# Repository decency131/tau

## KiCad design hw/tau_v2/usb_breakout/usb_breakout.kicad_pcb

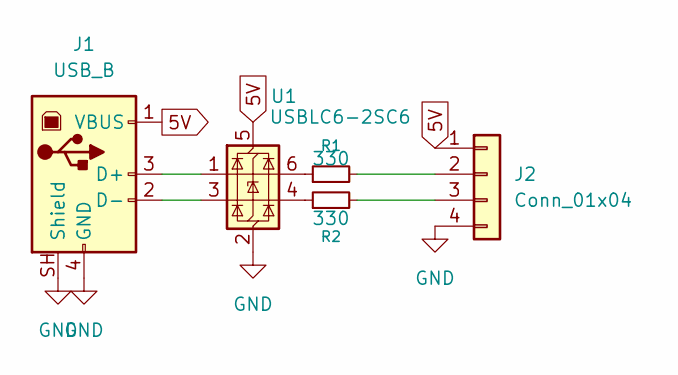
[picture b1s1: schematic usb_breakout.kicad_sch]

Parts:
J1: USB_B; USB_B_OST_USB-B1HSxx_Horizontal
J2: Conn_01x04; PinHeader_1x04_P2.00mm_Vertical
R1, R2: 330; R_0805_2012Metric_Pad1.20x1.40mm_HandSolder
U1: USBLC6-2SC6; SOT-23-6

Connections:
5V: J1.1 (VBUS), J2.1, U1.5 (VBUS)
GND: J1.4 (GND), J1.SH (Shield), J2.4, U1.2 (GND)
unnamed: J1.3 (D+), U1.1 (I/O1)
unnamed: J1.2 (D-), U1.3 (I/O2)
unnamed: J2.2, R1.2
unnamed: J2.3, R2.2
unnamed: R1.1, U1.6 (I/O1)
unnamed: R2.1, U1.4 (I/O2)

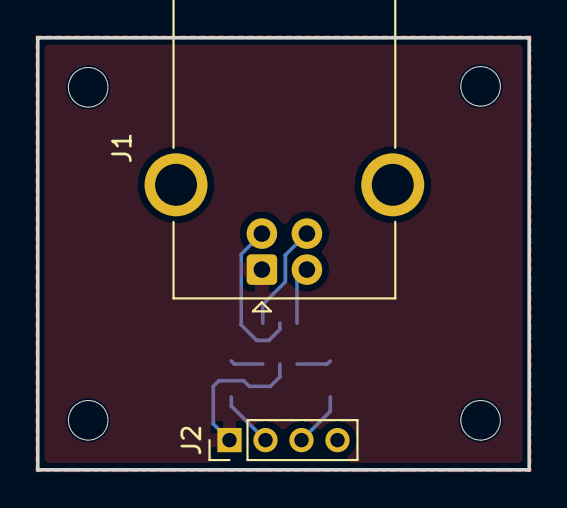
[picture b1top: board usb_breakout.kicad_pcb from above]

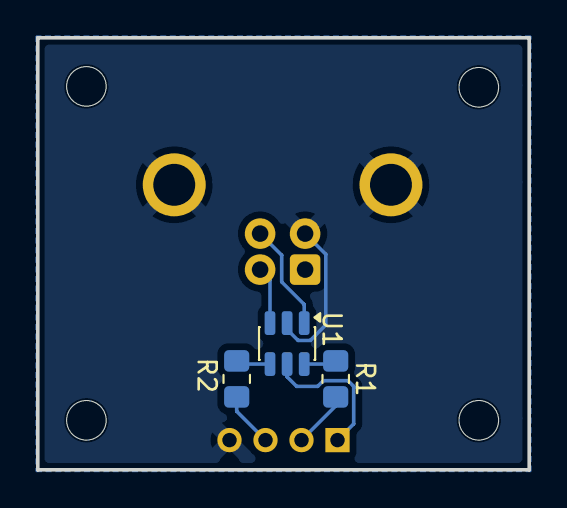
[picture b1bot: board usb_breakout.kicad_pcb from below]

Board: 2 copper layers, 27.3 x 24.0 mm, 9 parts (3 on the bottom side), 8 nets.

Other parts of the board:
M1, M2, M3, M4: MountingHole_2.2mm_M2

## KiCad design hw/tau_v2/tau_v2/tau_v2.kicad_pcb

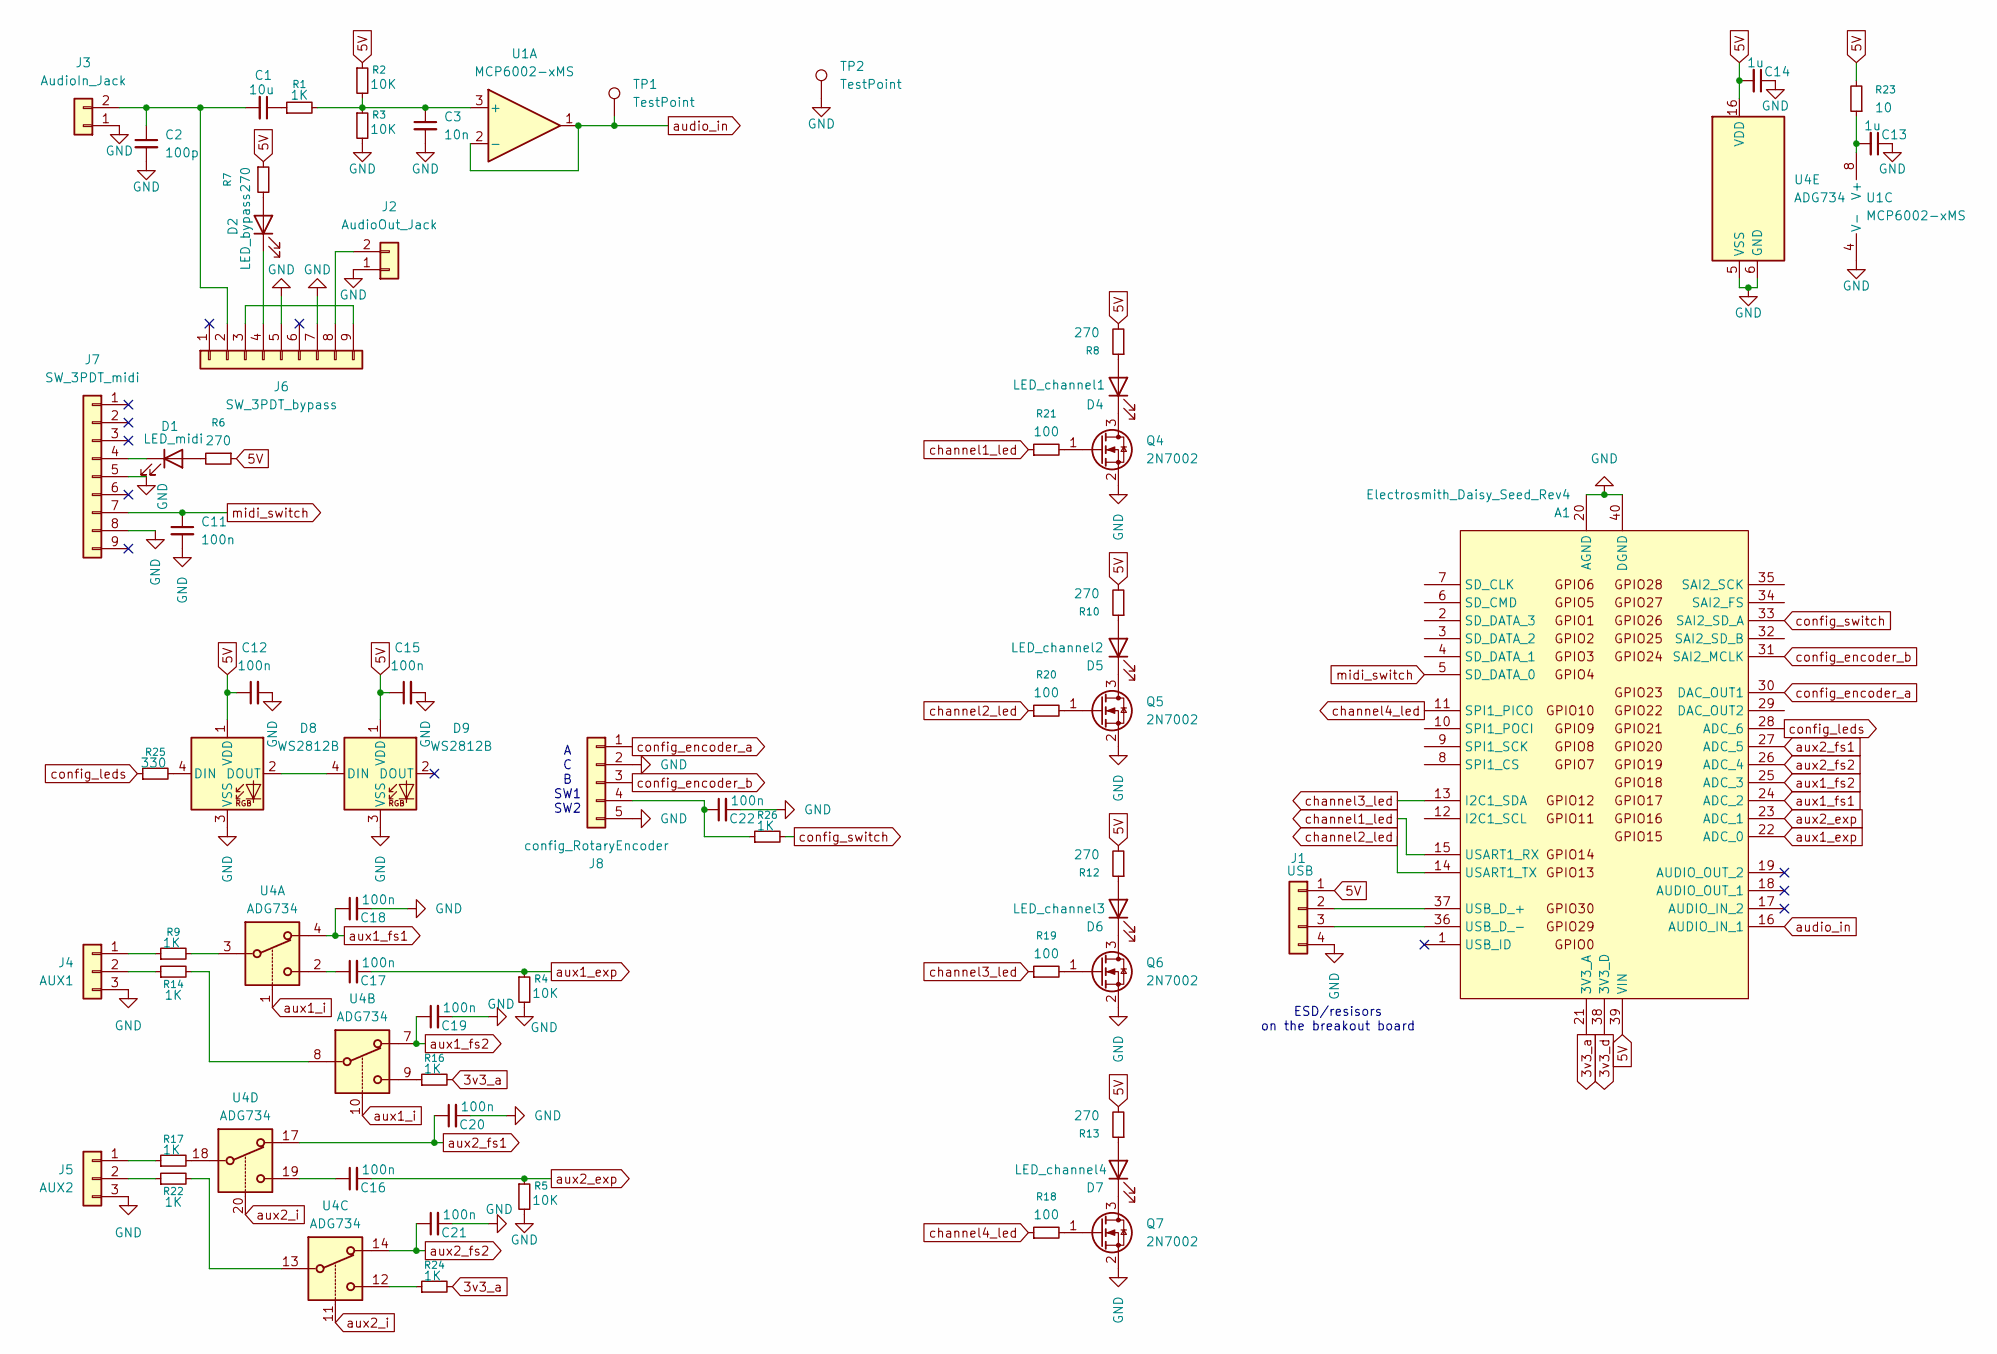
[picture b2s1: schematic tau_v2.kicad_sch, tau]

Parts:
A1: Electrosmith_Daisy_Seed_Rev4; Electrosmith_Daisy_Seed
C1: 10u; C_0805_2012Metric_Pad1.18x1.45mm_HandSolder
C2: 100p; C_0805_2012Metric_Pad1.18x1.45mm_HandSolder
C3: 10n; C_0805_2012Metric_Pad1.18x1.45mm_HandSolder
C11, C12, C15, C16, C17, C18, C19, C20, C21, C22: 100n; C_0805_2012Metric_Pad1.18x1.45mm_HandSolder
C13, C14: 1u; C_0805_2012Metric_Pad1.18x1.45mm_HandSolder
D1: LED_midi; PinHeader_1x02_P2.00mm_Vertical
D2: LED_bypass; PinHeader_1x02_P2.00mm_Vertical
D4: LED_channel1; PinHeader_1x02_P2.00mm_Vertical
D5: LED_channel2; PinHeader_1x02_P2.00mm_Vertical
D6: LED_channel3; PinHeader_1x02_P2.00mm_Vertical
D7: LED_channel4; PinHeader_1x02_P2.00mm_Vertical
D8, D9: WS2812B; PinHeader_1x04_P2.00mm_Vertical
J1: USB; PinHeader_1x04_P2.00mm_Vertical
J2: AudioOut_Jack; PinHeader_1x02_P2.00mm_Vertical
J3: AudioIn_Jack; PinHeader_1x02_P2.00mm_Vertical
J4: AUX1; PinHeader_1x03_P2.00mm_Vertical
J5: AUX2; PinHeader_1x03_P2.00mm_Vertical
J6: SW_3PDT_bypass; PinHeader_1x09_P2.00mm_Vertical
J7: SW_3PDT_midi; PinHeader_1x09_P2.00mm_Vertical
J8: config_RotaryEncoder; PinHeader_1x05_P2.00mm_Vertical
Q4, Q5, Q6, Q7: 2N7002; SOT-23
R1, R9, R14, R16, R17, R22, R24, R26: 1K; R_0805_2012Metric_Pad1.20x1.40mm_HandSolder
R2, R3, R4, R5: 10K; R_0805_2012Metric_Pad1.20x1.40mm_HandSolder
R6, R7, R8, R10, R12, R13: 270; R_0805_2012Metric_Pad1.20x1.40mm_HandSolder
R18, R19, R20, R21: 100; R_0805_2012Metric_Pad1.20x1.40mm_HandSolder
R23: 10; R_0805_2012Metric_Pad1.20x1.40mm_HandSolder
R25: 330; R_0805_2012Metric_Pad1.20x1.40mm_HandSolder
TP1, TP2: TestPoint; Pin_D1.0mm_L10.0mm_LooseFit
U1: MCP6002-xMS; MSOP-8-1EP_3x3mm_P0.65mm_EP1.5x1.8mm_handsoldered
U4: ADG734; TSSOP-20_4.4x6.5mm_P0.65mm

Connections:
3v3_a: A1.21 (3V3_A), R16.2, R24.2
3v3_d: A1.38 (3V3_D)
5V: A1.39 (VIN), C12.1, C14.2, C15.1, D8.1 (VDD), D9.1 (VDD), J1.1, R2.1, R6.1, R7.1, R8.2, R10.2, R12.2, R13.2, R23.2, U4.16 (VDD)
GND: A1.20 (AGND), A1.40 (DGND), C2.2, C3.2, C11.2, C12.2, C13.1, C14.1, C15.2, C18.2, C19.2, C20.2, C21.2, C22.2, D8.3 (VSS), D9.3 (VSS), J1.4, J2.1, J3.1, J4.3, J5.3, J6.5, J6.7, J7.5, J7.8, J8.2, J8.5, Q4.2 (S), Q5.2 (S), Q6.2 (S), Q7.2 (S), R3.2, R4.2, R5.2, TP2.1 (1_1), U1.4 (V-), U4.5 (VSS), U4.6 (GND)
unnamed: A1.37 (USB_D_+), J1.2
unnamed: A1.36 (USB_D_-), J1.3
unnamed: C1.1, R1.1
unnamed: C16.1, U4.19
unnamed: C17.1, U4.2
unnamed: D1.2 (A), R6.2
unnamed: D1.1 (K), J7.4
unnamed: D2.2 (A), R7.2
unnamed: D2.1 (K), J6.4
unnamed: D4.2 (A), R8.1
unnamed: D4.1 (K), Q4.3 (D)
unnamed: D5.2 (A), R10.1
unnamed: D5.1 (K), Q5.3 (D)
unnamed: D6.2 (A), R12.1
unnamed: D6.1 (K), Q6.3 (D)
unnamed: D7.2 (A), R13.1
unnamed: D7.1 (K), Q7.3 (D)
unnamed: D8.4 (DIN), R25.2
unnamed: D8.2 (DOUT), D9.4 (DIN)
unnamed: J2.2, J6.8
unnamed: C1.2, C2.1, J3.2, J6.2
unnamed: J4.1, R9.1
unnamed: J4.2, R14.1
unnamed: J5.1, R17.1
unnamed: J5.2, R22.1
unnamed: J6.3, J6.9
unnamed: C22.1, J8.4, R26.1
unnamed: Q4.1 (G), R21.2
unnamed: Q5.1 (G), R20.2
unnamed: Q6.1 (G), R19.2
unnamed: Q7.1 (G), R18.2
unnamed: R9.2, U4.3
unnamed: R14.2, U4.8
unnamed: R16.1, U4.9
unnamed: R17.2, U4.18
unnamed: R22.2, U4.13
unnamed: R24.1, U4.12
unnamed: C3.1, R1.2, R2.2, R3.1, U1.3 (+)
unnamed: C13.2, R23.1, U1.8 (V+)
audio_in: A1.16 (AUDIO_IN_1), TP1.1 (1_1), U1.1, U1.2 (-)
aux1_exp: A1.22 (ADC_0), C17.2, R4.1
aux1_fs1: A1.24 (ADC_2), C18.1, U4.4
aux1_fs2: A1.25 (ADC_3), C19.1, U4.7
aux1_i: U4.1, U4.10
aux2_exp: A1.23 (ADC_1), C16.2, R5.1
aux2_fs1: A1.27 (ADC_5), C20.1, U4.17
aux2_fs2: A1.26 (ADC_4), C21.1, U4.14
aux2_i: U4.11, U4.20
channel1_led: A1.15 (USART1_RX), R21.1
channel2_led: A1.14 (USART1_TX), R20.1
channel3_led: A1.13 (I2C1_SDA), R19.1
channel4_led: A1.11 (SPI1_PICO), R18.1
config_encoder_a: A1.30 (DAC_OUT1), J8.1
config_encoder_b: A1.31 (SAI2_MCLK), J8.3
config_leds: A1.28 (ADC_6), R25.1
config_switch: A1.33 (SAI2_SD_A), R26.2
midi_switch: A1.5 (SD_DATA_0), C11.1, J7.7

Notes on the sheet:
ESD/resisors on the breakout board
A C B SW1 SW2

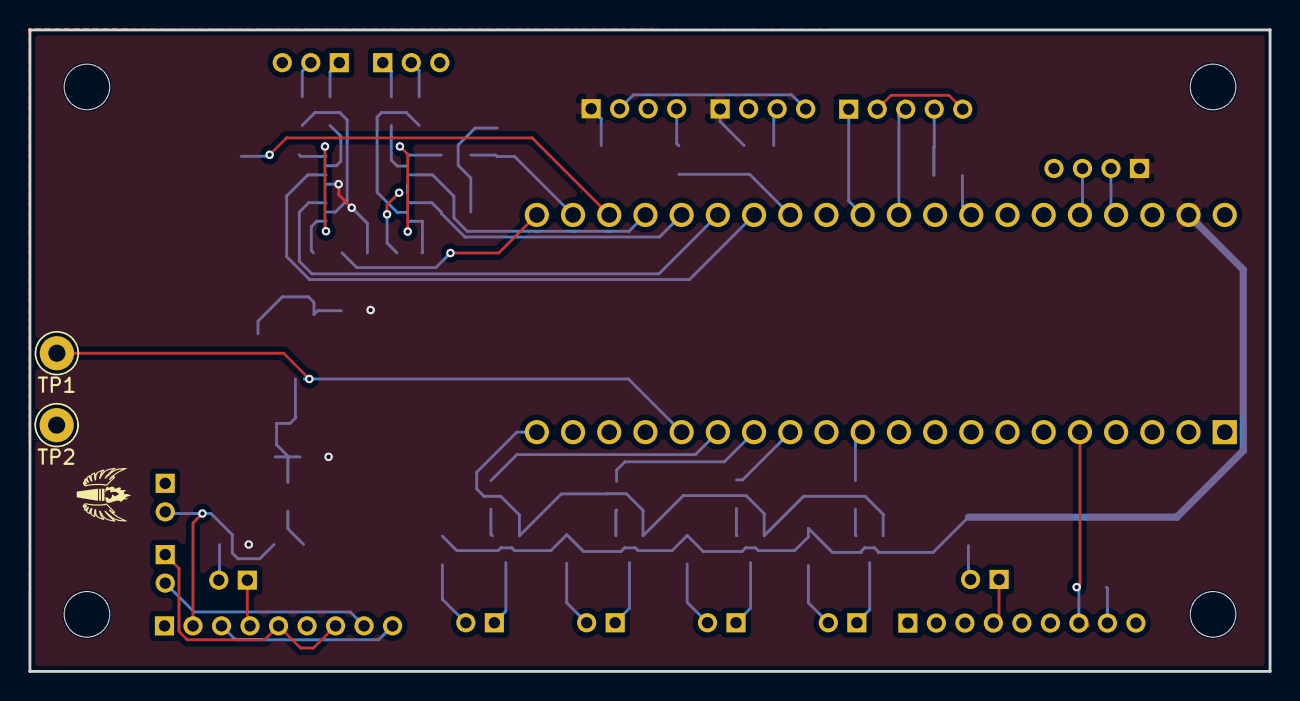
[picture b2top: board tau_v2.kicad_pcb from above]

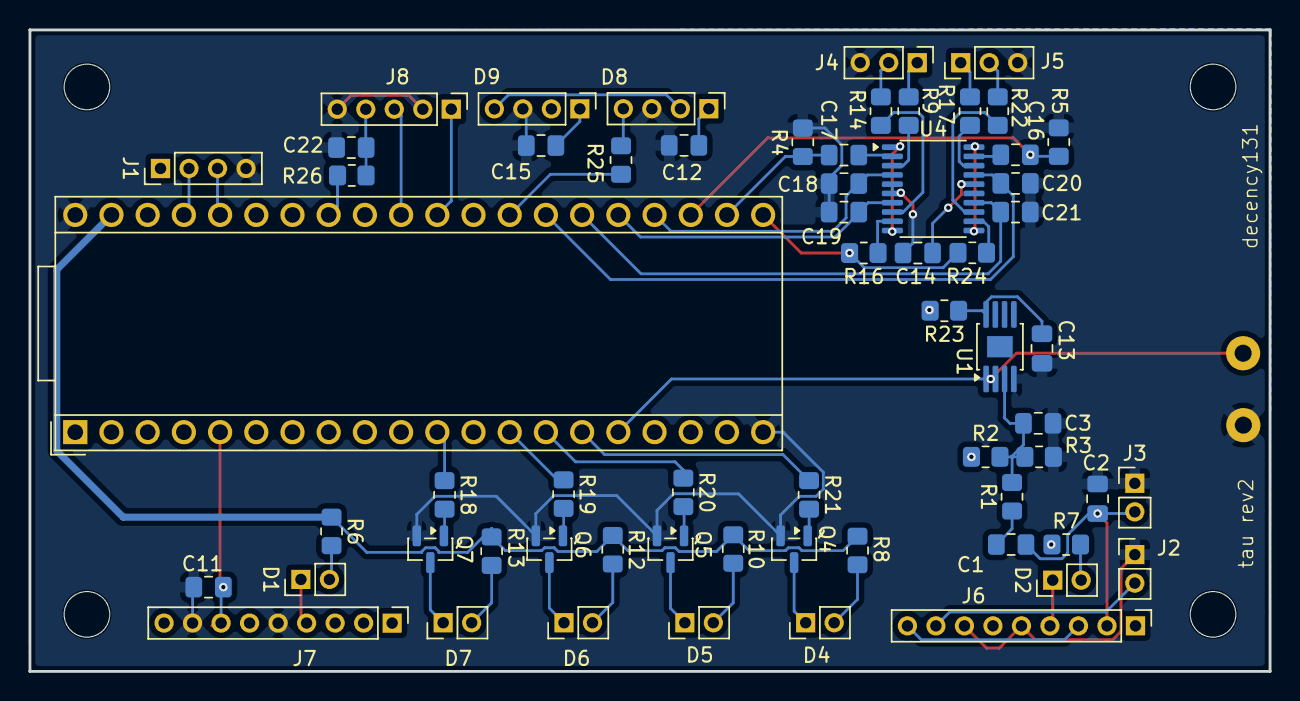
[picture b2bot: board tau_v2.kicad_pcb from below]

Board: 2 copper layers, 87.0 x 45.0 mm, 68 parts (62 on the bottom side), 60 nets.

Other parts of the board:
MH1, MH2, MH3, MH4: MountingHole_3.2mm_M3

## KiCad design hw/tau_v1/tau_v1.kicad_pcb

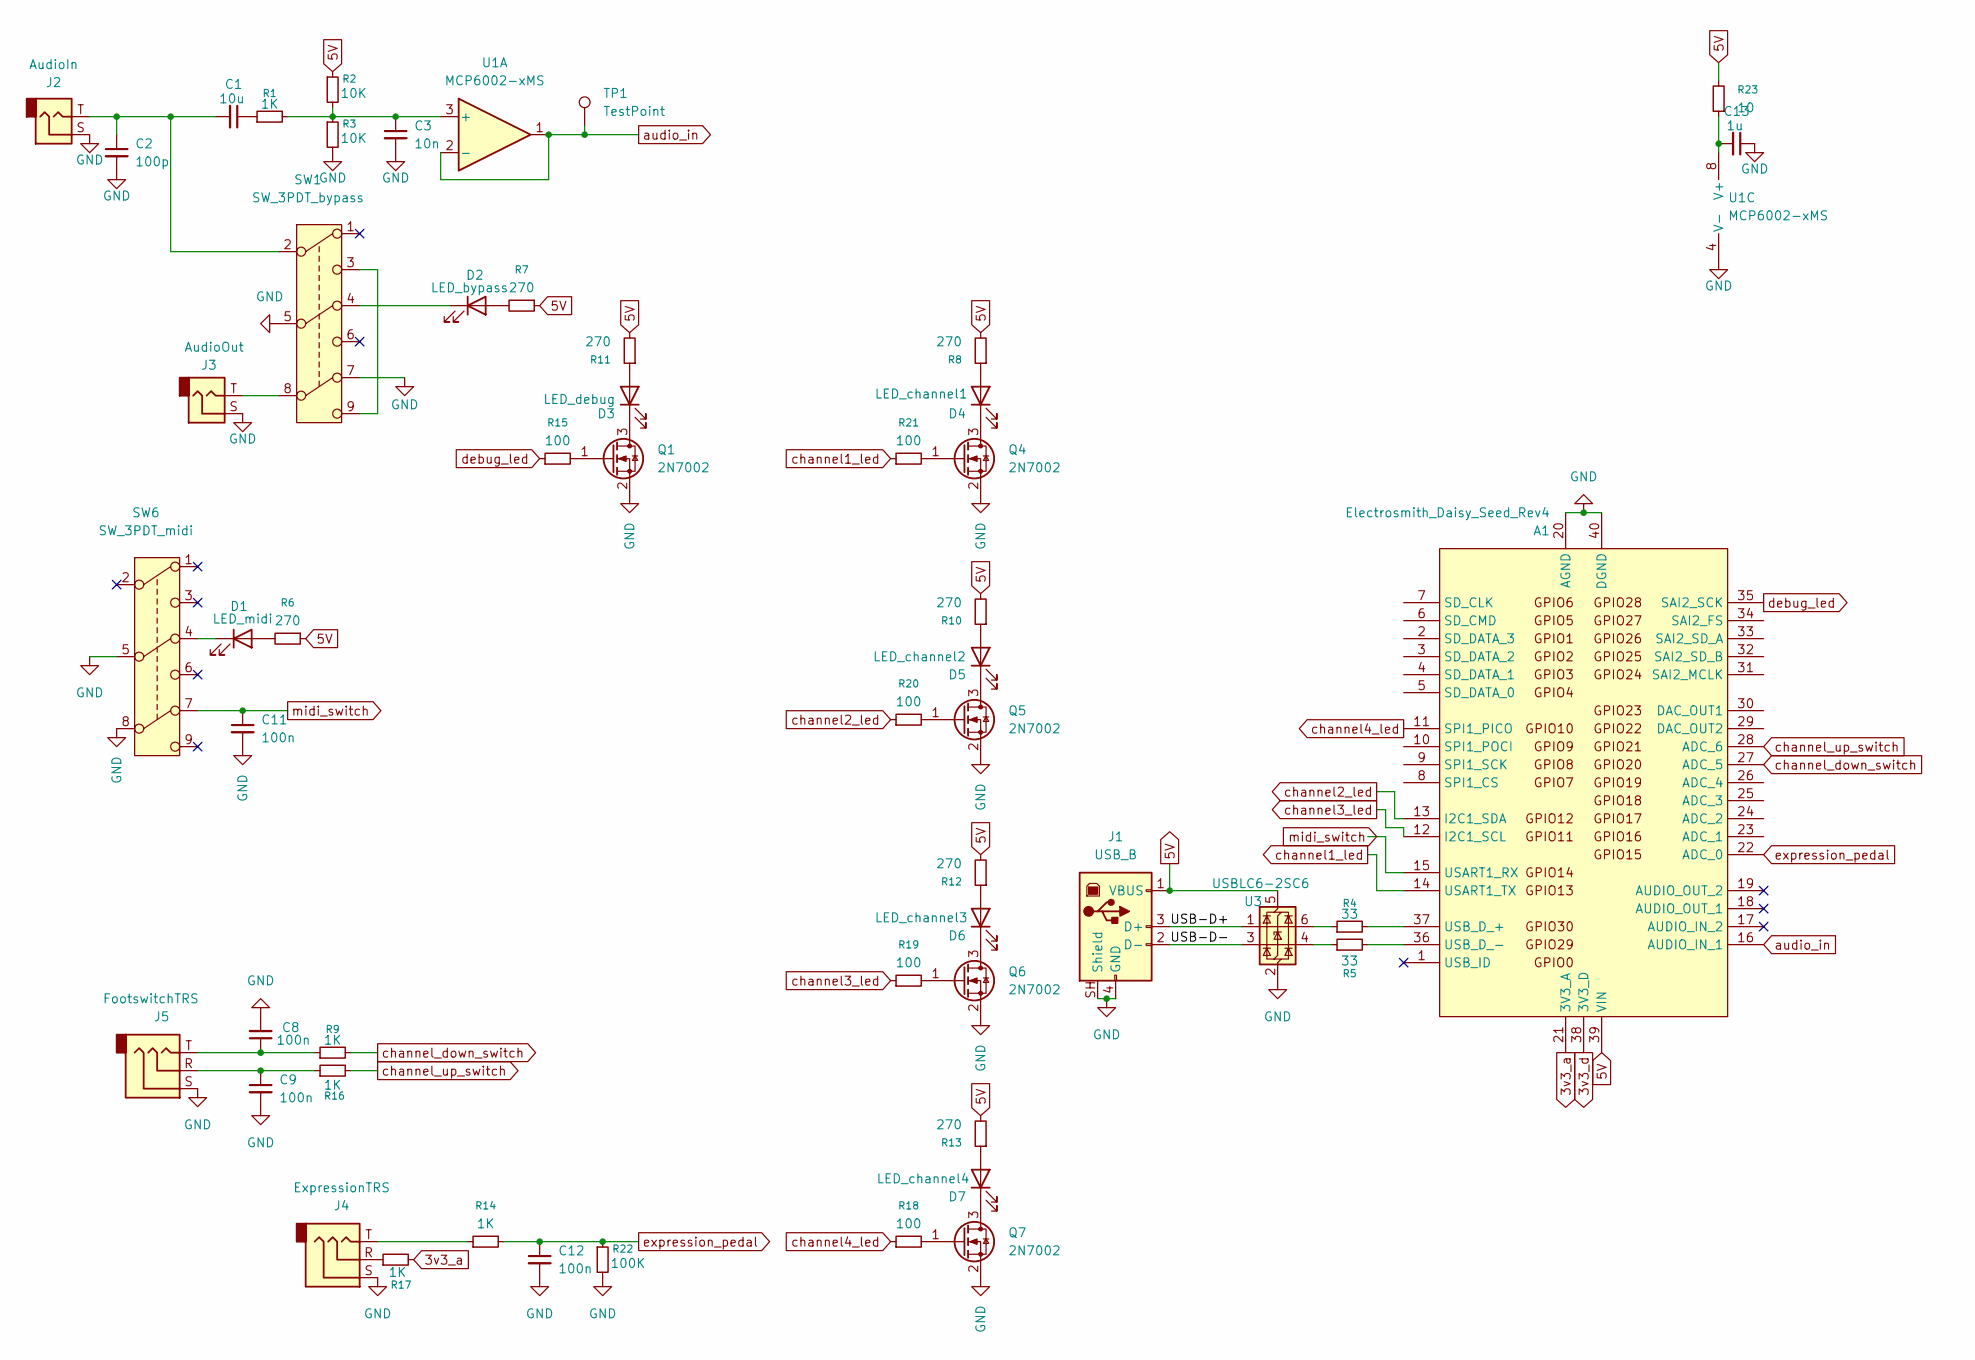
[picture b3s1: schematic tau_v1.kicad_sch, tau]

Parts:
A1: Electrosmith_Daisy_Seed_Rev4; Electrosmith_Daisy_Seed
C1: 10u; C_0805_2012Metric_Pad1.18x1.45mm_HandSolder
C2: 100p; C_0805_2012Metric_Pad1.18x1.45mm_HandSolder
C3: 10n; C_0805_2012Metric_Pad1.18x1.45mm_HandSolder
C8, C9, C11, C12: 100n; C_0805_2012Metric_Pad1.18x1.45mm_HandSolder
C13: 1u; C_0805_2012Metric_Pad1.18x1.45mm_HandSolder
D1: LED_midi; JST_XH_B2B-XH-A_1x02_P2.50mm_Vertical
D2: LED_bypass; JST_XH_B2B-XH-A_1x02_P2.50mm_Vertical
D3: LED_debug; LED_0805_2012Metric_Pad1.15x1.40mm_HandSolder
D4: LED_channel1; JST_XH_B2B-XH-A_1x02_P2.50mm_Vertical
D5: LED_channel2; JST_XH_B2B-XH-A_1x02_P2.50mm_Vertical
D6: LED_channel3; JST_XH_B2B-XH-A_1x02_P2.50mm_Vertical
D7: LED_channel4; JST_XH_B2B-XH-A_1x02_P2.50mm_Vertical
J1: USB_B; USB_B_OST_USB-B1HSxx_Horizontal
J2: AudioIn; Jack_6.35mm_Neutrik_NMJ4HFD2_Horizontal
J3: AudioOut; Jack_6.35mm_Neutrik_NMJ4HFD2_Horizontal
J4: ExpressionTRS; Jack_6.35mm_Neutrik_NRJ6HH-AU_Horizontal
J5: FootswitchTRS; Jack_6.35mm_Neutrik_NRJ6HH-AU_Horizontal
Q1, Q4, Q5, Q6, Q7: 2N7002; SOT-23
R1, R9, R14, R16, R17: 1K; R_0805_2012Metric_Pad1.20x1.40mm_HandSolder
R2, R3: 10K; R_0805_2012Metric_Pad1.20x1.40mm_HandSolder
R4, R5: 33; R_0805_2012Metric_Pad1.20x1.40mm_HandSolder
R6, R7, R8, R10, R11, R12, R13: 270; R_0805_2012Metric_Pad1.20x1.40mm_HandSolder
R15, R18, R19, R20, R21: 100; R_0805_2012Metric_Pad1.20x1.40mm_HandSolder
R22: 100K; R_0805_2012Metric_Pad1.20x1.40mm_HandSolder
R23: 10; R_0805_2012Metric_Pad1.20x1.40mm_HandSolder
SW1: SW_3PDT_bypass; SW_3PDT
SW6: SW_3PDT_midi; SW_3PDT
TP1: TestPoint; Pin_D1.0mm_L10.0mm_LooseFit
U1: MCP6002-xMS; MSOP-8-1EP_3x3mm_P0.65mm_EP1.5x1.8mm_handsoldered
U3: USBLC6-2SC6; SOT-23-6

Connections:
3v3_a: A1.21 (3V3_A), R17.2
3v3_d: A1.38 (3V3_D)
5V: A1.39 (VIN), J1.1 (VBUS), R2.1, R6.1, R7.1, R8.2, R10.2, R11.2, R12.2, R13.2, R23.2, U3.5 (VBUS)
/USB-D+: J1.3 (D+), U3.1 (I/O1)
/USB-D-: J1.2 (D-), U3.3 (I/O2)
GND: A1.20 (AGND), A1.40 (DGND), C2.2, C3.2, C8.2, C9.2, C11.2, C12.2, C13.1, J1.4 (GND), J1.SH (Shield), J2.S, J3.S, J4.S, J5.S, Q1.2 (S), Q4.2 (S), Q5.2 (S), Q6.2 (S), Q7.2 (S), R3.2, R22.2, SW1.5, SW1.7, SW6.5, SW6.8, U1.4 (V-), U3.2 (GND)
unnamed: A1.37 (USB_D_+), R4.2
unnamed: A1.36 (USB_D_-), R5.2
unnamed: C1.1, R1.1
unnamed: C1.2, C2.1, J2.T, SW1.2
unnamed: C8.1, J5.T, R9.1
unnamed: C9.1, J5.R, R16.1
unnamed: D1.2 (A), R6.2
unnamed: D1.1 (K), SW6.4
unnamed: D2.2 (A), R7.2
unnamed: D2.1 (K), SW1.4
unnamed: D3.2 (A), R11.1
unnamed: D3.1 (K), Q1.3 (D)
unnamed: D4.2 (A), R8.1
unnamed: D4.1 (K), Q4.3 (D)
unnamed: D5.2 (A), R10.1
unnamed: D5.1 (K), Q5.3 (D)
unnamed: D6.2 (A), R12.1
unnamed: D6.1 (K), Q6.3 (D)
unnamed: D7.2 (A), R13.1
unnamed: D7.1 (K), Q7.3 (D)
unnamed: J3.T, SW1.8
unnamed: J4.R, R17.1
unnamed: J4.T, R14.1
unnamed: Q1.1 (G), R15.2
unnamed: Q4.1 (G), R21.2
unnamed: Q5.1 (G), R20.2
unnamed: Q6.1 (G), R19.2
unnamed: Q7.1 (G), R18.2
unnamed: R4.1, U3.6 (I/O1)
unnamed: R5.1, U3.4 (I/O2)
unnamed: SW1.3, SW1.9
unnamed: C3.1, R1.2, R2.2, R3.1, U1.3 (+)
unnamed: C13.2, R23.1, U1.8 (V+)
audio_in: A1.16 (AUDIO_IN_1), TP1.1 (1_1), U1.1, U1.2 (-)
channel1_led: A1.14 (USART1_TX), R21.1
channel2_led: A1.13 (I2C1_SDA), R20.1
channel3_led: A1.12 (I2C1_SCL), R19.1
channel4_led: A1.11 (SPI1_PICO), R18.1
channel_down_switch: A1.27 (ADC_5), R9.2
channel_up_switch: A1.28 (ADC_6), R16.2
debug_led: A1.35 (SAI2_SCK), R15.1
expression_pedal: A1.22 (ADC_0), C12.1, R14.2, R22.1
midi_switch: A1.15 (USART1_RX), C11.1, SW6.7

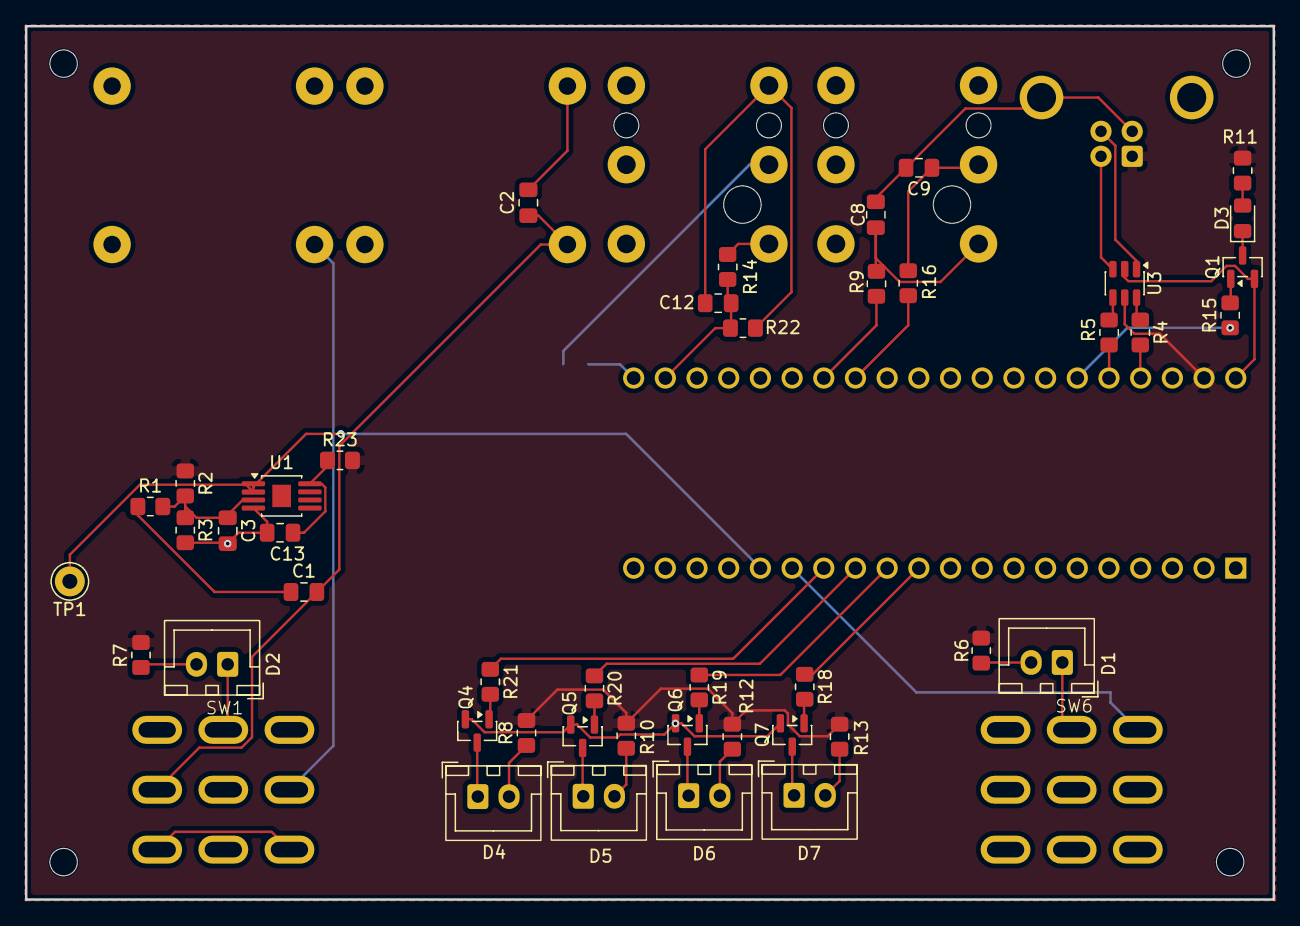
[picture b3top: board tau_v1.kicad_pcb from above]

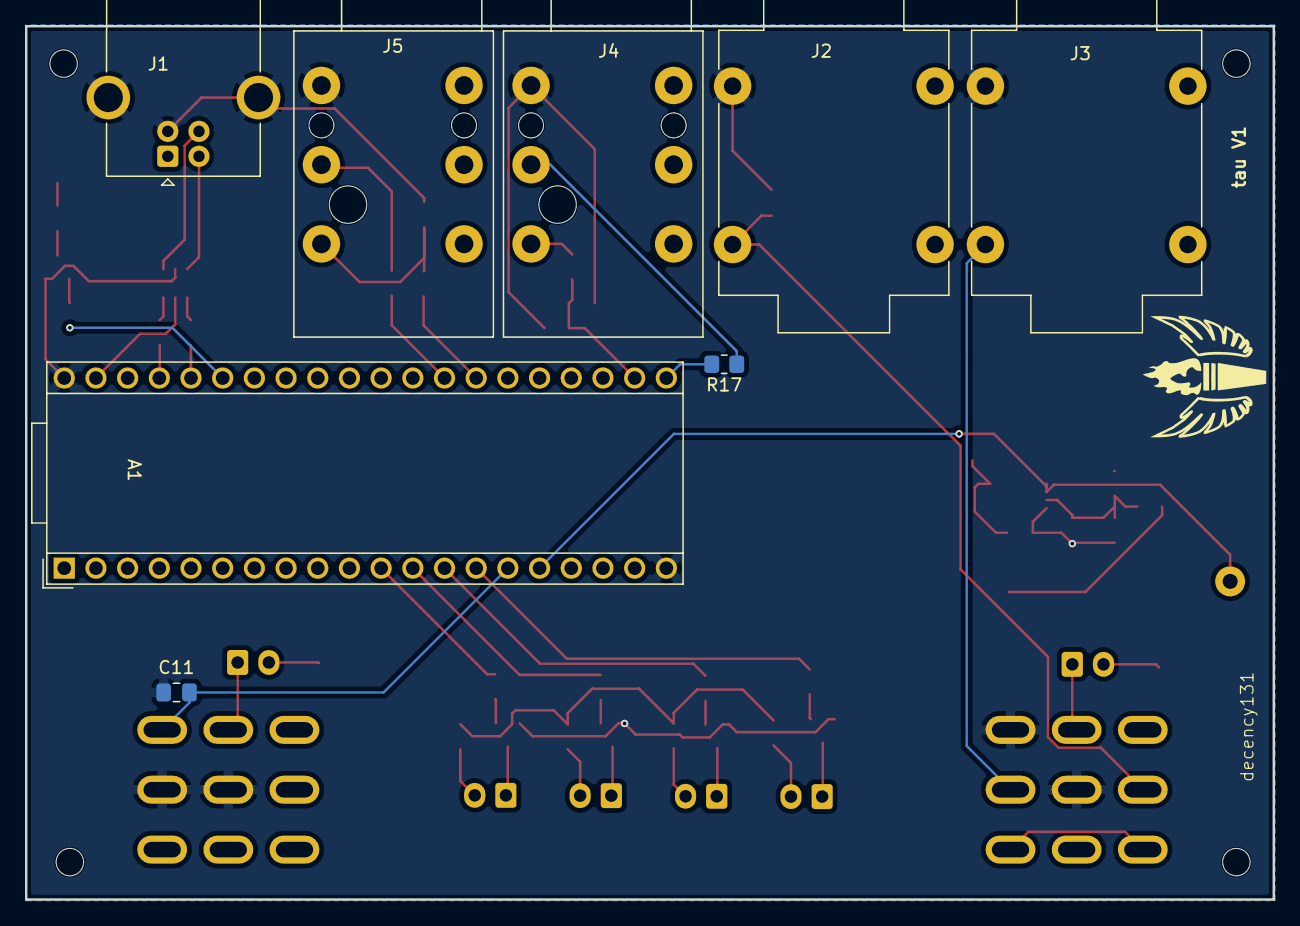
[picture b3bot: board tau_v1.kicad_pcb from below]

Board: 2 copper layers, 100.0 x 70.0 mm, 58 parts (8 on the bottom side), 48 nets.

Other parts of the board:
MH1, MH2, MH3, MH4: MountingHole_2.2mm_M2

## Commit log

2026-02-21 init
2026-03-22 first pcb design
2026-03-29 god is dead and we killed him. new pcb.
2026-04-06 hardware_final_final
2026-05-03 update gitignore
2026-05-07 rev 2 + base software
2026-05-08 midi enable switch
2026-05-09 minor audio otimisation
2026-05-09 could read adc
2026-05-10 could do footswitches
2026-05-10 I must enjoy torturing myself
2026-05-11 be sure to loop
2026-05-21 theoretically might work
    - finished drivers and for everything, if i'n mot blind
2026-05-23 who has two thumbs and is a genius? not this guy!
    - reworked midi messages
    - this should be a base and works well for syntesised instruments and
    kind of works with a real guitar
    - still needs some optimisation for use with bass guitars and in general
    lower pitch instruments
2026-05-24 This will definitely break in 2024 (TODO)
    - cleanup
    - added readme and license
2026-05-24 Useful text
2026-05-24 REALLY FUCKING FIXED
2026-05-24 Enable MIDI detection in pitch analysisminor fixes of stuff I commented before while debugging
